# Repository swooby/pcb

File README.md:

# PCBs

NOTE: Unless otherwise specified, **all of these boards are UNTESTED**!

## TODO
* ESP32 with onboard level shifting
* DoubleWing Color Screen with buttons

## Adafruit DoubleWing INA219x4 (quad) Ammeter
Hopefully similar to Adafruit's INA219 FeatherWing (https://www.adafruit.com/product/3650)

## Adafruit FeatherWing INA219x2 (dual) Ammeter
...

## TinyPICO INA219 Ammeter
Hopefully similar to Adafruit's INA219 FeatherWing (https://www.adafruit.com/product/3650)

## TinyPICO 74HCT245 Level Shifter

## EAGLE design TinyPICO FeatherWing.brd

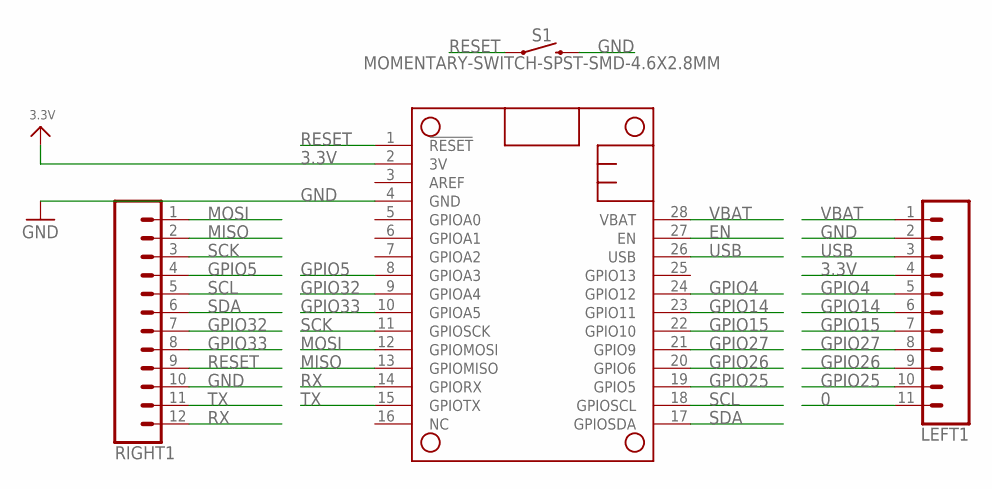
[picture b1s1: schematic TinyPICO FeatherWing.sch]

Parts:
LEFT1: CONN_11; 1X11
MS2: FEATHERWING
RIGHT1: CONN_12; 1X12
S1: MOMENTARY-SWITCH-SPST-SMD-4.6X2.8MM; TACTILE_SWITCH_SMD_4.6X2.8MM

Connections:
0: LEFT1.11
3.3V: LEFT1.4, MS2.2 (3V)
EN: MS2.27 (EN)
GND: LEFT1.2, MS2.4 (GND), RIGHT1.10, S1.3 (2), S1.4 (2)
GPIO4: LEFT1.5, MS2.24 (GPIO12)
GPIO5: MS2.8 (GPIOA3), RIGHT1.4
GPIO14: LEFT1.6, MS2.23 (GPIO11)
GPIO15: LEFT1.7, MS2.22 (GPIO10)
GPIO25: LEFT1.10, MS2.19 (GPIO5)
GPIO26: LEFT1.9, MS2.20 (GPIO6)
GPIO27: LEFT1.8, MS2.21 (GPIO9)
GPIO32: MS2.9 (GPIOA4), RIGHT1.7
GPIO33: MS2.10 (GPIOA5), RIGHT1.8
MISO: MS2.13 (GPIOMISO), RIGHT1.2
MOSI: MS2.12 (GPIOMOSI), RIGHT1.1
RESET: MS2.1 (!RESET), RIGHT1.9, S1.1, S1.2 (1)
RX: MS2.14 (GPIORX), RIGHT1.12
SCK: MS2.11 (GPIOSCK), RIGHT1.3
SCL: MS2.18 (GPIOSCL), RIGHT1.5
SDA: MS2.17 (GPIOSDA), RIGHT1.6
TX: MS2.15 (GPIOTX), RIGHT1.11
USB: LEFT1.3, MS2.26 (USB)
VBAT: LEFT1.1, MS2.28 (VBAT)

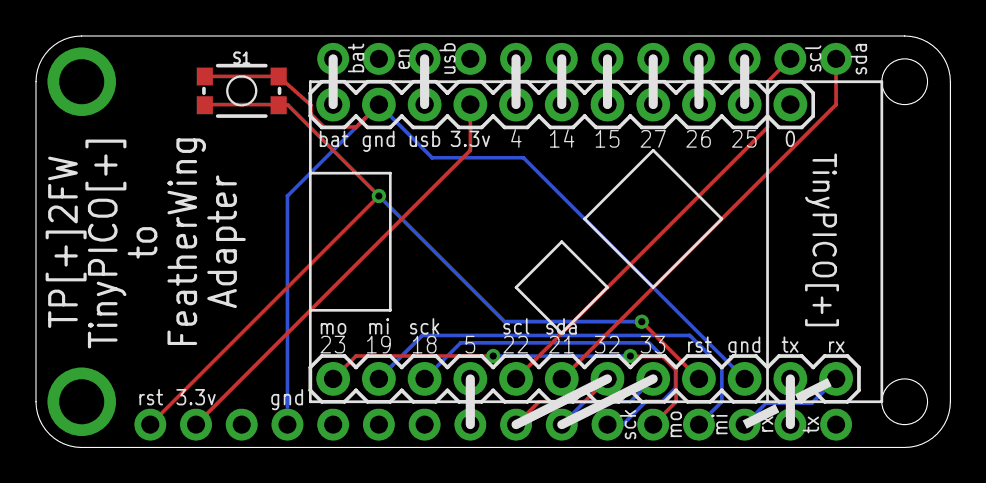
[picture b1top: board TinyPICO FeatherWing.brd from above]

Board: 2 copper layers, 50.8 x 22.9 mm, 4 parts (0 on the bottom side), 21 nets.

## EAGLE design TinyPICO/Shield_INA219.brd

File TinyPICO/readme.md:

* https://github.com/tinypico/tinypico-hardware

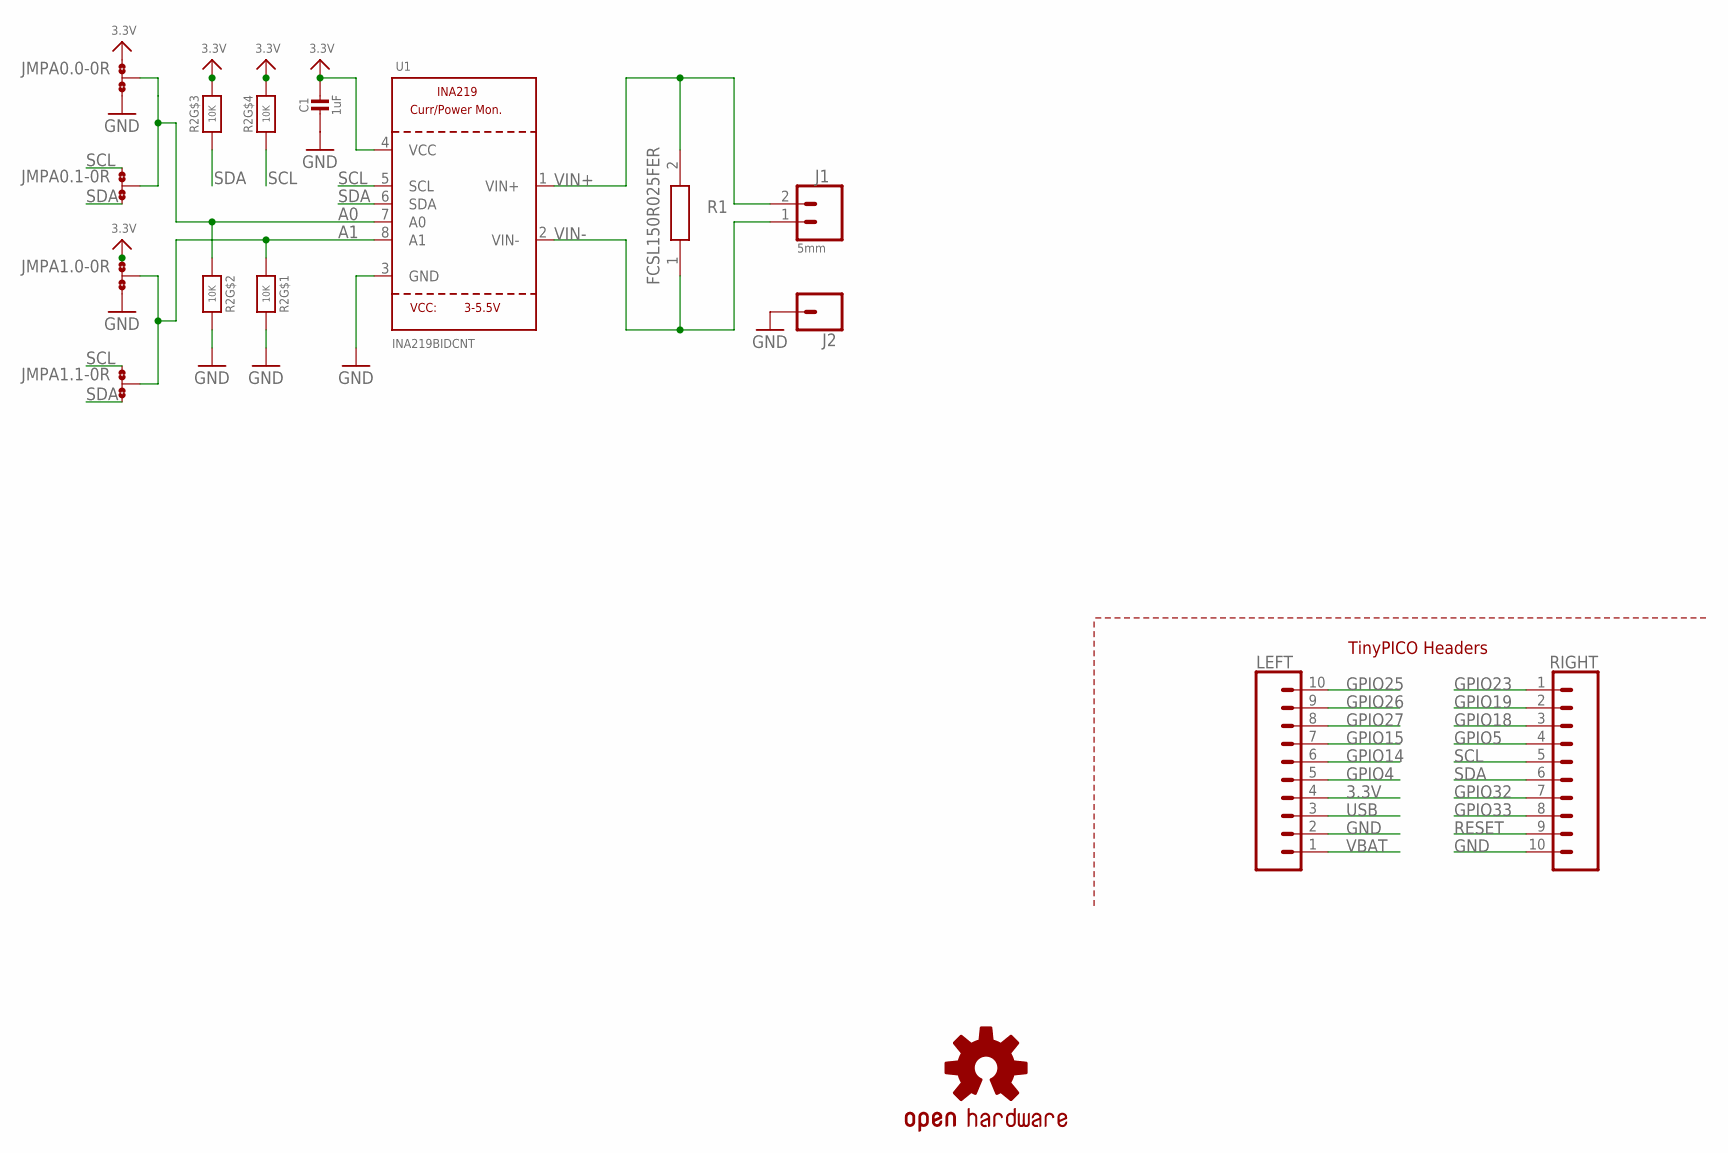
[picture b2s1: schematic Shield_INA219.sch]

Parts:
C1: 1uF; 0805-NO@1
J1: 5mm; SCREWTERMINAL-5MM-2
J2: CONN_01; 1X01
JMPA0.0, JMPA0.1, JMPA1.0, JMPA1.1: 0R-JUMPD; C0R-JMP_NONE
LEFT: TINYPICO_HEADER_10NO_SILK_PTH_FEMALE; 1X10_NO_SILK
LOGO1: OSHW-LOGOS; OSHW-LOGO-S
R1: FCSL150R025FER; RESC90152X87N
R2: 10K; RESPACK_4X0603
RIGHT: TINYPICO_HEADER_10NO_SILK_PTH_FEMALE; 1X10_NO_SILK
U1: INA219BIDCNT; SOT23-8

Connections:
3.3V: C1.1, JMPA0.0.1, JMPA1.0.1, LEFT.4, R2.5 (2), R2.6 (2), U1.4 (VCC)
A0: JMPA0.0.2, JMPA0.1.2, R2.2 (1), U1.7 (A0)
A1: JMPA1.0.2, JMPA1.1.2, R2.1, U1.8 (A1)
GND: C1.2, J2.1, JMPA0.0.3, JMPA1.0.3, LEFT.2, R2.7 (2), R2.8 (2), RIGHT.10, U1.3 (GND)
GPIO4: LEFT.5
GPIO5: RIGHT.4
GPIO14: LEFT.6
GPIO15: LEFT.7
GPIO18: RIGHT.3
GPIO19: RIGHT.2
GPIO23: RIGHT.1
GPIO25: LEFT.10
GPIO26: LEFT.9
GPIO27: LEFT.8
GPIO32: RIGHT.7
GPIO33: RIGHT.8
RESET: RIGHT.9
SCL: JMPA0.1.1, JMPA1.1.1, R2.4 (1), RIGHT.5, U1.5 (SCL)
SDA: JMPA0.1.3, JMPA1.1.3, R2.3 (1), RIGHT.6, U1.6 (SDA)
USB: LEFT.3
VBAT: LEFT.1
VIN+: J1.2, R1.2, U1.1 (VIN+)
VIN-: J1.1, R1.1, U1.2 (VIN-)

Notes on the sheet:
TinyPICO Headers

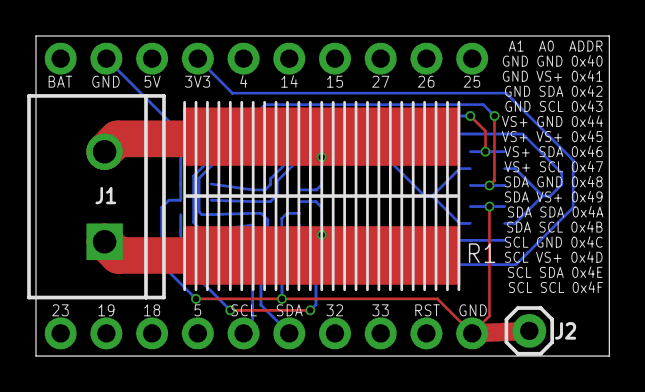
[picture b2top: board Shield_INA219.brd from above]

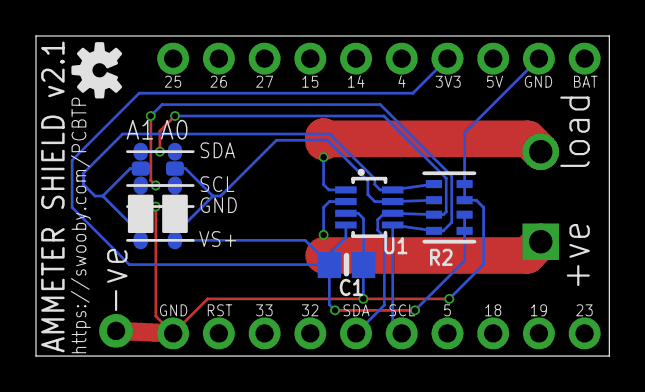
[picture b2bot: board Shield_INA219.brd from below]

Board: 2 copper layers, 31.9 x 17.8 mm, 13 parts (8 on the bottom side), 8 nets.

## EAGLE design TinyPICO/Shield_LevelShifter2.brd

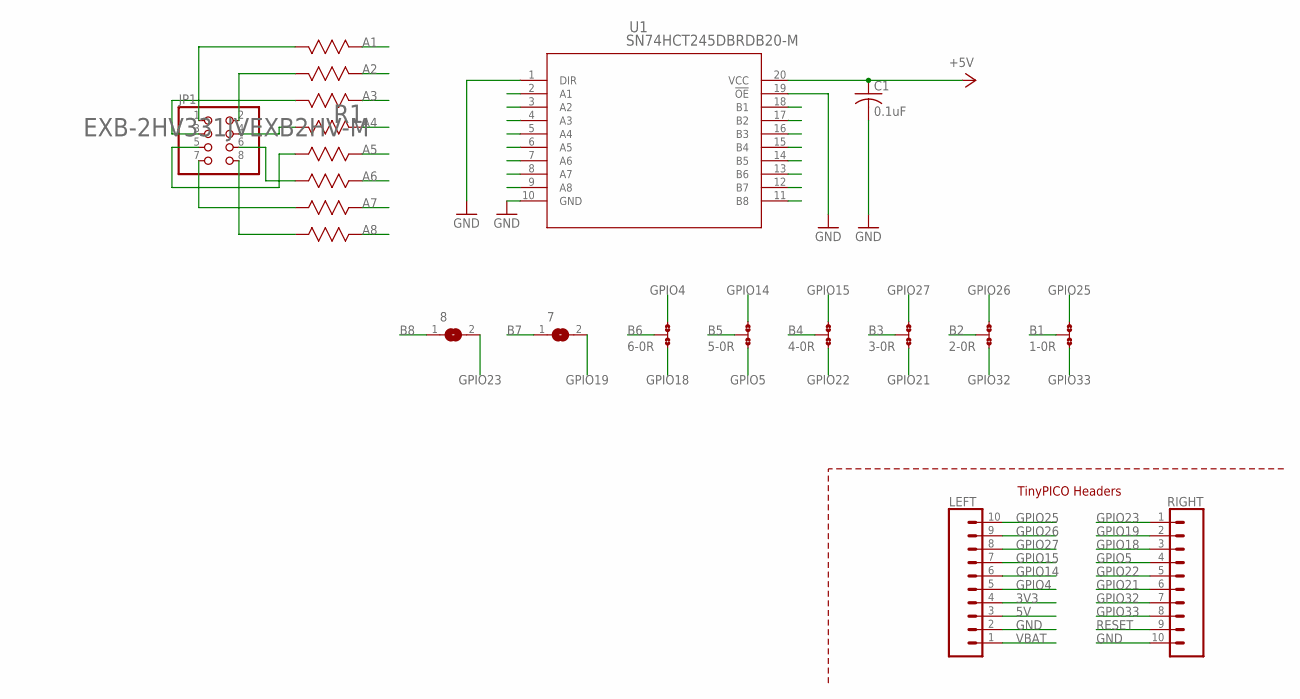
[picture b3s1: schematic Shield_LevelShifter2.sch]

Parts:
1, 2, 3, 4, 5, 6: 0R-JUMPD; C0R-JMP_NONE
7, 8: SJ
C1: 0.1uF; C0603
JP1: PINHD-2X4/90; 2X04/90
LEFT: TINYPICO_HEADER_10NO_SILK_PTH_FEMALE; 1X10_NO_SILK
R1: EXB-2HV331JVEXB2HV-M; EXB2HV-M
RIGHT: TINYPICO_HEADER_10NO_SILK_PTH_FEMALE; 1X10_NO_SILK
U1: SN74HCT245DBRDB20-M; DB20-M

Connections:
3V3: LEFT.4
5V: C1.1, LEFT.3, U1.20 (VCC)
A1: R1.1, U1.2 (A1)
A2: R1.2, U1.3 (A2)
A3: R1.3, U1.4 (A3)
A4: R1.4, U1.5 (A4)
A5: R1.5, U1.6 (A5)
A6: R1.6, U1.7 (A6)
A7: R1.7, U1.8 (A7)
A8: R1.8, U1.9 (A8)
B1: 1.2, U1.18 (B1)
B2: 2.2, U1.17 (B2)
B3: 3.2, U1.16 (B3)
B4: 4.2, U1.15 (B4)
B5: 5.2, U1.14 (B5)
B6: 6.2, U1.13 (B6)
B7: 7.1, U1.12 (B7)
B8: 8.1, U1.11 (B8)
GND: C1.2, LEFT.2, RIGHT.10, U1.1 (DIR), U1.10 (GND), U1.19 (!OE)
GPIO4: 6.3, LEFT.5
GPIO5: 5.1, RIGHT.4
GPIO14: 5.3, LEFT.6
GPIO15: 4.3, LEFT.7
GPIO18: 6.1, RIGHT.3
GPIO19: 7.2, RIGHT.2
GPIO21: 3.1, RIGHT.6
GPIO22: 4.1, RIGHT.5
GPIO23: 8.2, RIGHT.1
GPIO25: 1.3, LEFT.10
GPIO26: 2.3, LEFT.9
GPIO27: 3.3, LEFT.8
GPIO32: 2.1, RIGHT.7
GPIO33: 1.1, RIGHT.8
unnamed: JP1.1, R1.16
unnamed: JP1.4, R1.13
unnamed: JP1.2, R1.15
unnamed: JP1.3, R1.14
unnamed: JP1.5, R1.12
unnamed: JP1.6, R1.11
unnamed: JP1.7, R1.10
unnamed: JP1.8, R1.9
RESET: RIGHT.9
VBAT: LEFT.1

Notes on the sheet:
TinyPICO Headers

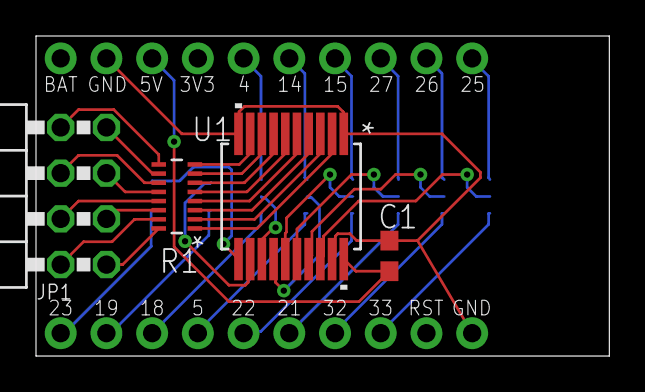
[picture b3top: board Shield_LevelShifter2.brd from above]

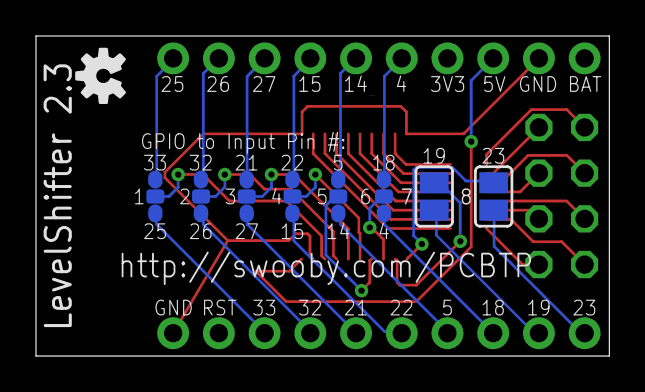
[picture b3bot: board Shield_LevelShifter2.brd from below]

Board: 2 copper layers, 31.9 x 17.8 mm, 15 parts (9 on the bottom side), 40 nets.

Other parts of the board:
LOGO: OSHW-LOGOS; OSHW-LOGO-S

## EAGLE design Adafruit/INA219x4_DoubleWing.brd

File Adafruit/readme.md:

* https://github.com/adafruit/Adafruit-INA219-Current-Sensor-PCB
* https://github.com/adafruit/Adafruit-FeatherWing-Proto-Doubler-and-Tripler

* https://github.com/adafruit/Adafruit-HUZZAH32-ESP32-Feather-PCB
* https://github.com/adafruit/Adafruit-Terminal-Block-FeatherWing-PCB
* https://github.com/adafruit/Adafruit-OLED-FeatherWing-PCB
* https://github.com/adafruit/Adafruit_FeatherOLED
* https://github.com/adafruit/Adafruit-NeoPixel-FeatherWing-PCB
* https://github.com/adafruit/Adafruit-Ethernet-FeatherWing-PCB
* https://github.com/adafruit/Adafruit-RGB-Matrix-FeatherWing-PCB
* https://github.com/adafruit/Adafruit-3.5in-TFT-Featherwing-PCB
* https://github.com/adafruit/Adafruit-2.4-TFT-FeatherWing-PCB
* https://github.com/adafruit/Adafruit-Mini-TFT-with-Joystick-Featherwing-PCB
* https://github.com/adafruit/Adafruit-Joy-Featherwing-PCB

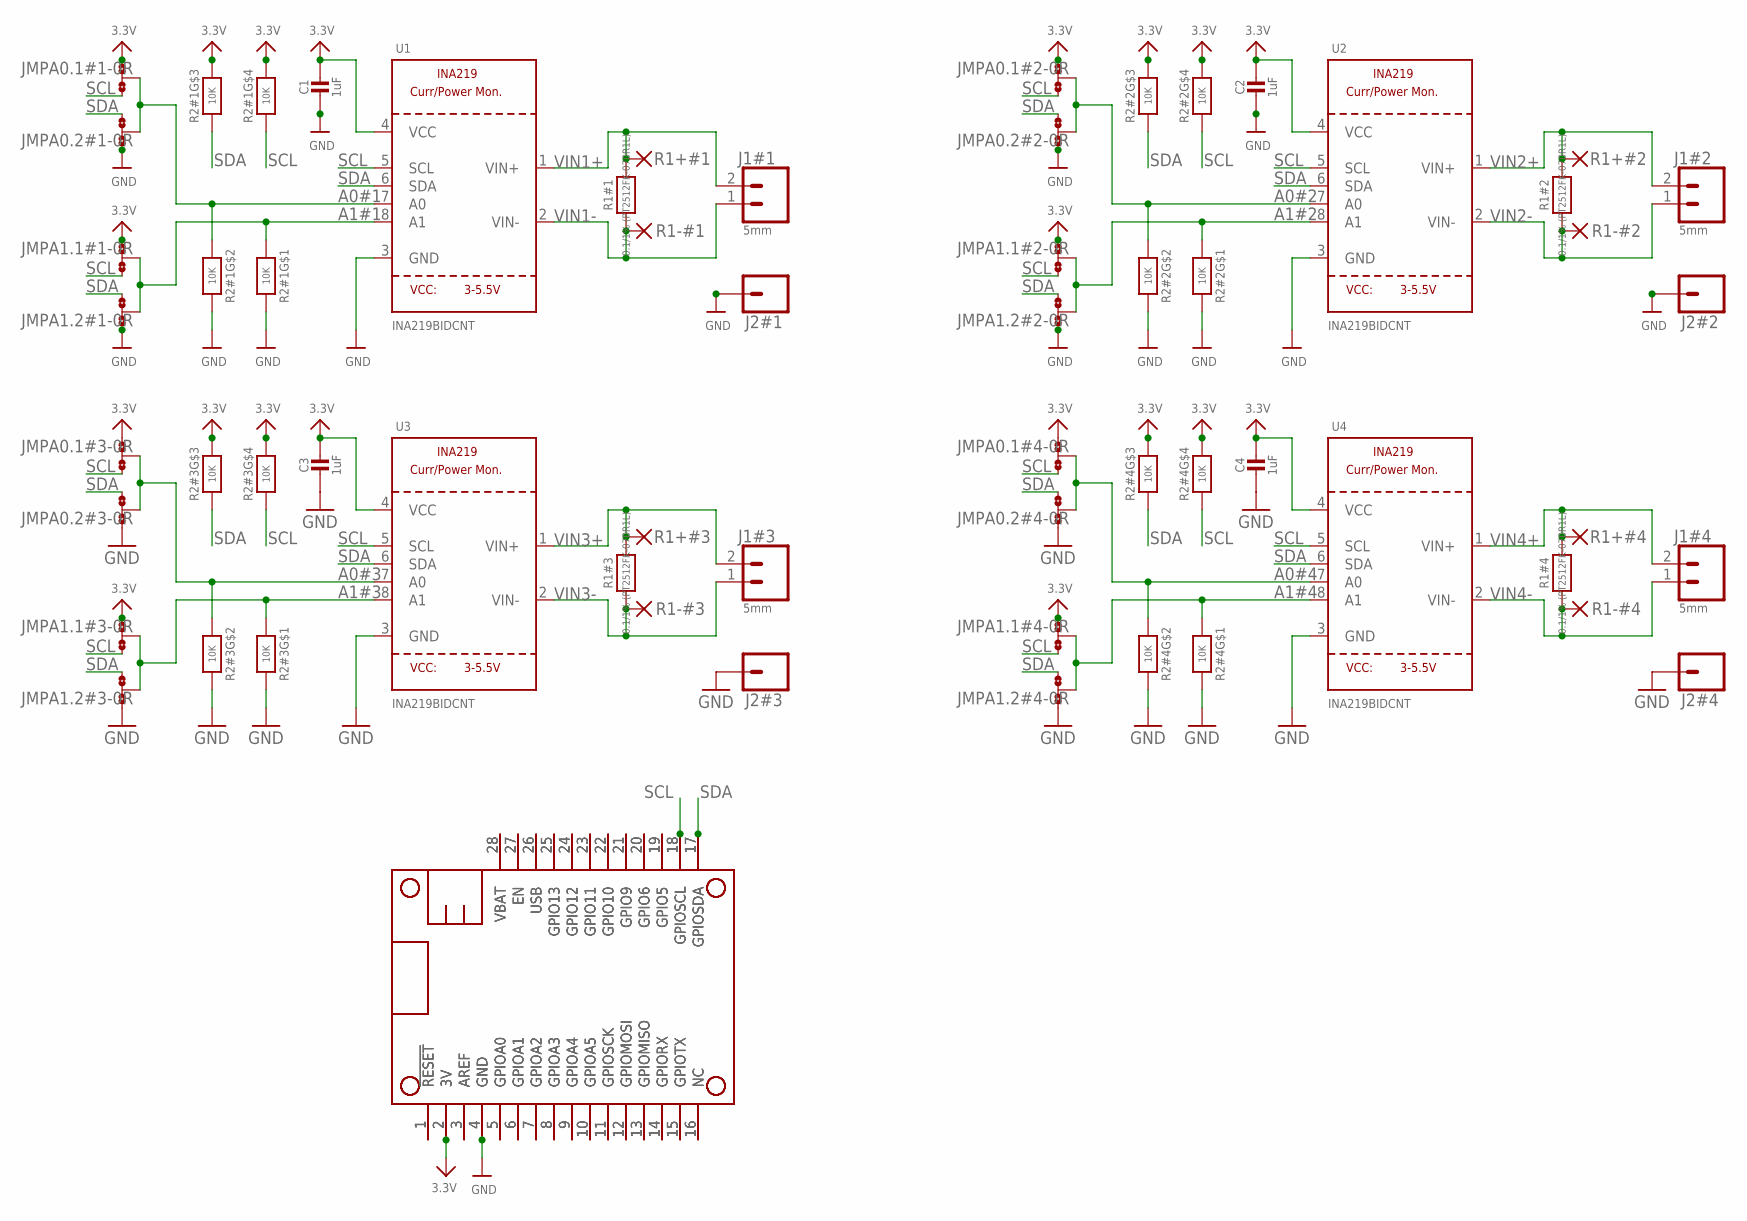
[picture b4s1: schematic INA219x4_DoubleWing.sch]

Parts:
C1, C2, C3, C4: 1uF; 0805-NO@1
J1#1, J1#2, J1#3, J1#4: 5mm; SCREWTERMINAL-5MM-2
J2#1, J2#2, J2#3, J2#4: CONN_01; 1X01
JMPA0.1#1, JMPA0.1#2, JMPA0.1#3, JMPA0.1#4, JMPA0.2#1, JMPA0.2#2, JMPA0.2#3, JMPA0.2#4, JMPA1.1#1, JMPA1.1#2, JMPA1.1#3, JMPA1.1#4, JMPA1.2#1, JMPA1.2#2, JMPA1.2#3, JMPA1.2#4: 0R-JUMPD; C0R-JMP_NONE
MS1, MS2: FEATHERWING_NODIM; FEATHERWING_DIM
R1#1, R1#2, R1#3, R1#4: 0.1/1% (PT2512FK-070R1L); 2512
R1+#1, R1+#2, R1+#3, R1+#4, R1-#1, R1-#2, R1-#3, R1-#4: 1,6/0,9
R2#1, R2#2, R2#3, R2#4: 10K; RESPACK_4X0603
U1, U2, U3, U4: INA219BIDCNT; SOT23-8

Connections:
3.3V: C1.1, C2.1, C3.1, C4.1, JMPA0.1#1.1, JMPA0.1#2.1, JMPA0.1#3.1, JMPA0.1#4.1, JMPA1.1#1.1, JMPA1.1#2.1, JMPA1.1#3.1, JMPA1.1#4.1, MS1.2 (3V), MS2.2 (3V), R2#1.5 (2), R2#1.6 (2), R2#2.5 (2), R2#2.6 (2), R2#3.5 (2), R2#3.6 (2), R2#4.5 (2), R2#4.6 (2), U1.4 (VCC), U2.4 (VCC), U3.4 (VCC), U4.4 (VCC)
A0#1: JMPA0.1#1.2, JMPA0.2#1.2, R2#1.2 (1), U1.7 (A0)
A0#2: JMPA0.1#2.2, JMPA0.2#2.2, R2#2.2 (1), U2.7 (A0)
A0#3: JMPA0.1#3.2, JMPA0.2#3.2, R2#3.2 (1), U3.7 (A0)
A0#4: JMPA0.1#4.2, JMPA0.2#4.2, R2#4.2 (1), U4.7 (A0)
A1#1: JMPA1.1#1.2, JMPA1.2#1.2, R2#1.1, U1.8 (A1)
A1#2: JMPA1.1#2.2, JMPA1.2#2.2, R2#2.1, U2.8 (A1)
A1#3: JMPA1.1#3.2, JMPA1.2#3.2, R2#3.1, U3.8 (A1)
A1#4: JMPA1.1#4.2, JMPA1.2#4.2, R2#4.1, U4.8 (A1)
GND: C1.2, C2.2, C3.2, C4.2, J2#1.1, J2#2.1, J2#3.1, J2#4.1, JMPA0.2#1.3, JMPA0.2#2.3, JMPA0.2#3.3, JMPA0.2#4.3, JMPA1.2#1.3, JMPA1.2#2.3, JMPA1.2#3.3, JMPA1.2#4.3, MS1.4 (GND), MS2.4 (GND), R2#1.7 (2), R2#1.8 (2), R2#2.7 (2), R2#2.8 (2), R2#3.7 (2), R2#3.8 (2), R2#4.7 (2), R2#4.8 (2), U1.3 (GND), U2.3 (GND), U3.3 (GND), U4.3 (GND)
unnamed: MS1.27 (EN), MS2.27 (EN)
unnamed: MS1.16 (NC), MS2.16 (NC)
unnamed: MS1.25 (GPIO13), MS2.25 (GPIO13)
unnamed: MS1.15 (GPIOTX), MS2.15 (GPIOTX)
unnamed: MS1.24 (GPIO12), MS2.24 (GPIO12)
unnamed: MS1.14 (GPIORX), MS2.14 (GPIORX)
unnamed: MS1.13 (GPIOMISO), MS2.13 (GPIOMISO)
unnamed: MS1.12 (GPIOMOSI), MS2.12 (GPIOMOSI)
unnamed: MS1.11 (GPIOSCK), MS2.11 (GPIOSCK)
unnamed: MS1.10 (GPIOA5), MS2.10 (GPIOA5)
unnamed: MS1.9 (GPIOA4), MS2.9 (GPIOA4)
unnamed: MS1.8 (GPIOA3), MS2.8 (GPIOA3)
unnamed: MS1.7 (GPIOA2), MS2.7 (GPIOA2)
unnamed: MS1.6 (GPIOA1), MS2.6 (GPIOA1)
unnamed: MS1.5 (GPIOA0), MS2.5 (GPIOA0)
unnamed: MS1.3 (AREF), MS2.3 (AREF)
unnamed: MS1.1 (!RESET), MS2.1 (!RESET)
unnamed: MS1.23 (GPIO11), MS2.23 (GPIO11)
unnamed: MS1.22 (GPIO10), MS2.22 (GPIO10)
unnamed: MS1.21 (GPIO9), MS2.21 (GPIO9)
unnamed: MS1.20 (GPIO6), MS2.20 (GPIO6)
unnamed: MS1.19 (GPIO5), MS2.19 (GPIO5)
SCL: JMPA0.1#1.3, JMPA0.1#2.3, JMPA0.1#3.3, JMPA0.1#4.3, JMPA1.1#1.3, JMPA1.1#2.3, JMPA1.1#3.3, JMPA1.1#4.3, MS1.18 (GPIOSCL), MS2.18 (GPIOSCL), R2#1.4 (1), R2#2.4 (1), R2#3.4 (1), R2#4.4 (1), U1.5 (SCL), U2.5 (SCL), U3.5 (SCL), U4.5 (SCL)
SDA: JMPA0.2#1.1, JMPA0.2#2.1, JMPA0.2#3.1, JMPA0.2#4.1, JMPA1.2#1.1, JMPA1.2#2.1, JMPA1.2#3.1, JMPA1.2#4.1, MS1.17 (GPIOSDA), MS2.17 (GPIOSDA), R2#1.3 (1), R2#2.3 (1), R2#3.3 (1), R2#4.3 (1), U1.6 (SDA), U2.6 (SDA), U3.6 (SDA), U4.6 (SDA)
USB: MS1.26 (USB), MS2.26 (USB)
VBAT: MS1.28 (VBAT), MS2.28 (VBAT)
VIN1+: J1#1.2, R1#1.2, R1+#1.1, U1.1 (VIN+)
VIN1-: J1#1.1, R1#1.1, R1-#1.1, U1.2 (VIN-)
VIN2+: J1#2.2, R1#2.2, R1+#2.1, U2.1 (VIN+)
VIN2-: J1#2.1, R1#2.1, R1-#2.1, U2.2 (VIN-)
VIN3+: J1#3.2, R1#3.2, R1+#3.1, U3.1 (VIN+)
VIN3-: J1#3.1, R1#3.1, R1-#3.1, U3.2 (VIN-)
VIN4+: J1#4.2, R1#4.2, R1+#4.1, U4.1 (VIN+)
VIN4-: J1#4.1, R1#4.1, R1-#4.1, U4.2 (VIN-)

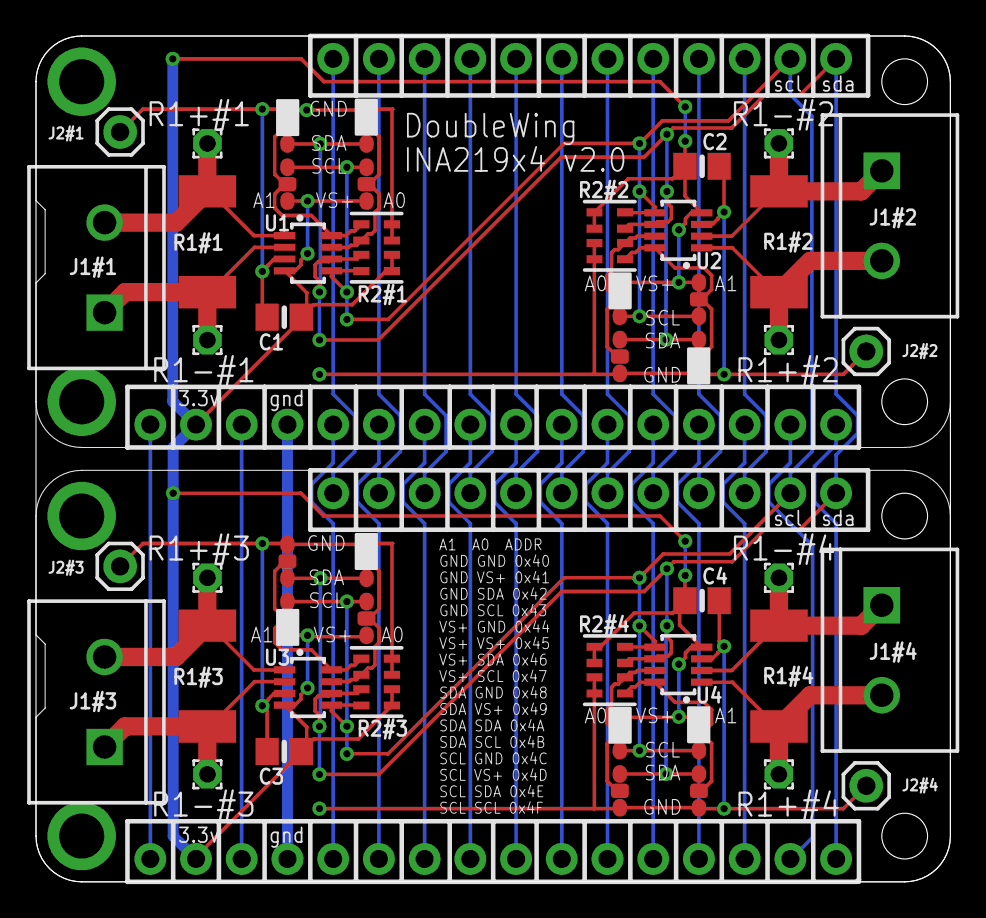
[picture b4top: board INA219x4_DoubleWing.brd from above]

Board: 2 copper layers, 50.8 x 47.0 mm, 50 parts (0 on the bottom side), 44 nets.

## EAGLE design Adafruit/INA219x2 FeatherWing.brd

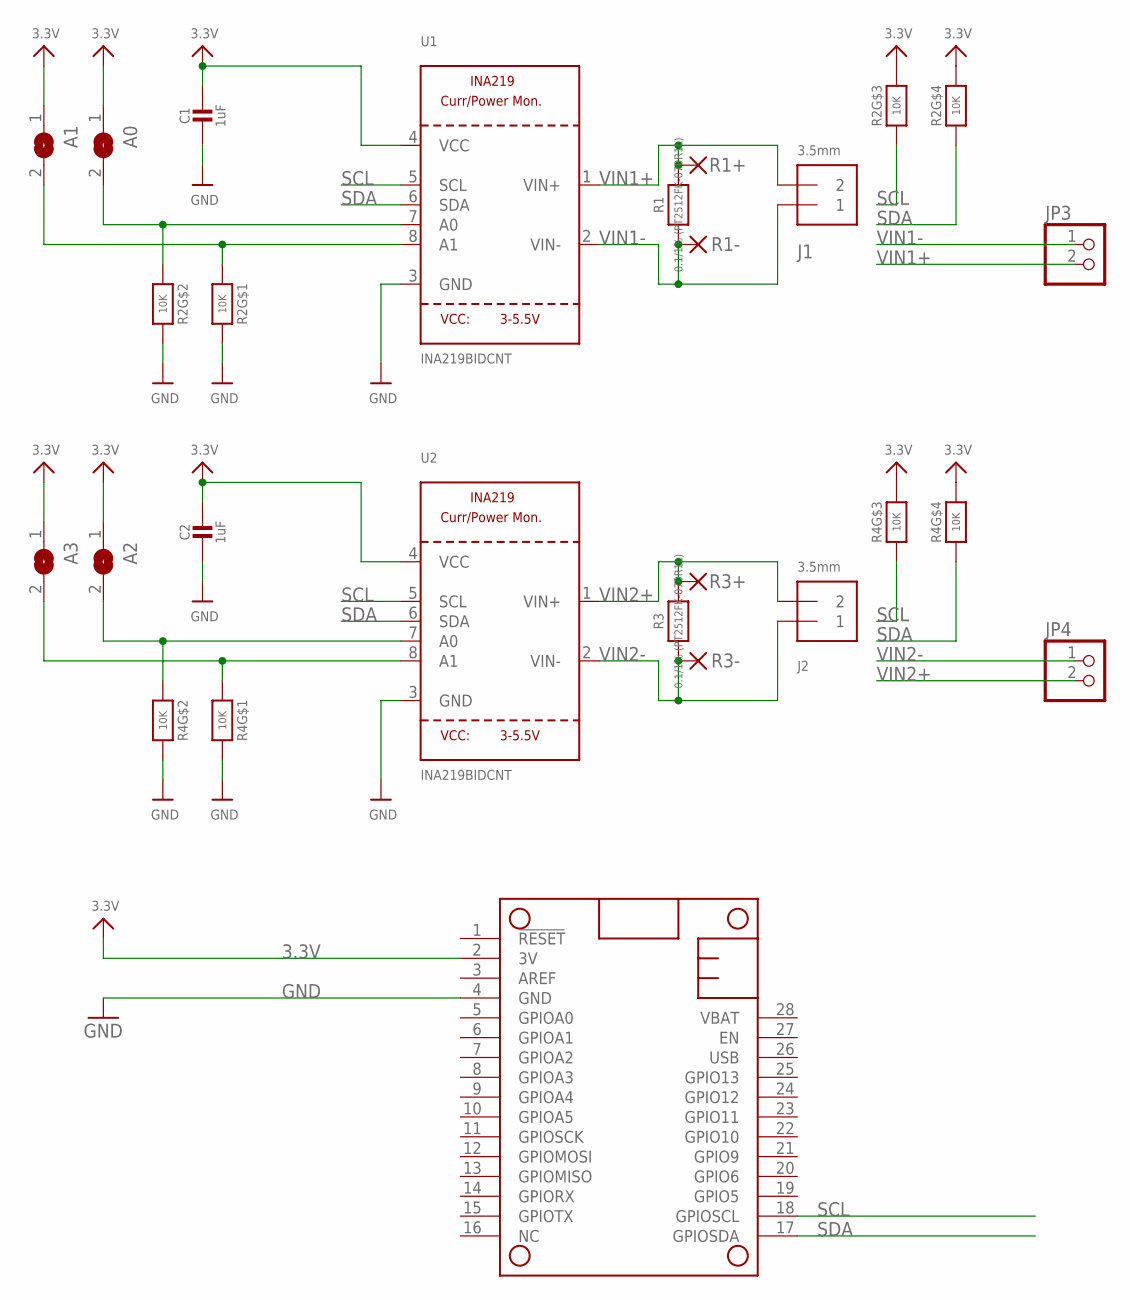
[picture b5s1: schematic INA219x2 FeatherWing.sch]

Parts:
A0, A1, A2, A3: SOLDERJUMPERREFLOW_NOPASTE; SOLDERJUMPER_REFLOW_NOPASTE
C1, C2: 1uF; 0805-NO@1
J1, J2: 3.5mm; TERMBLOCK_1X2-3.5MM
JP3, JP4: HEADER-1X2ROUND; 1X02_ROUND
MS1: FEATHERWING
R1, R3: 0.1/1% (PT2512FK-070R1L); 2512
R1+, R1-, R3+, R3-: 1,6/0,9
R2, R4: 10K; RESPACK_4X0603
U1, U2: INA219BIDCNT; SOT23-8

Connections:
3.3V: A0.1, A1.1, A2.1, A3.1, C1.1, C2.1, MS1.2 (3V), R2.5 (2), R2.6 (2), R4.5 (2), R4.6 (2), U1.4 (VCC), U2.4 (VCC)
GND: C1.2, C2.2, MS1.4 (GND), R2.7 (2), R2.8 (2), R4.7 (2), R4.8 (2), U1.3 (GND), U2.3 (GND)
unnamed: A1.2, R2.1, U1.8 (A1)
unnamed: A0.2, R2.2 (1), U1.7 (A0)
unnamed: A3.2, R4.1, U2.8 (A1)
unnamed: A2.2, R4.2 (1), U2.7 (A0)
SCL: MS1.18 (GPIOSCL), R2.3 (1), R4.3 (1), U1.5 (SCL), U2.5 (SCL)
SDA: MS1.17 (GPIOSDA), R2.4 (1), R4.4 (1), U1.6 (SDA), U2.6 (SDA)
VIN1+: J1.2, JP3.2, R1.2, R1+.1, U1.1 (VIN+)
VIN1-: J1.1, JP3.1, R1.1, R1-.1, U1.2 (VIN-)
VIN2+: J2.2, JP4.2, R3.2, R3+.1, U2.1 (VIN+)
VIN2-: J2.1, JP4.1, R3.1, R3-.1, U2.2 (VIN-)

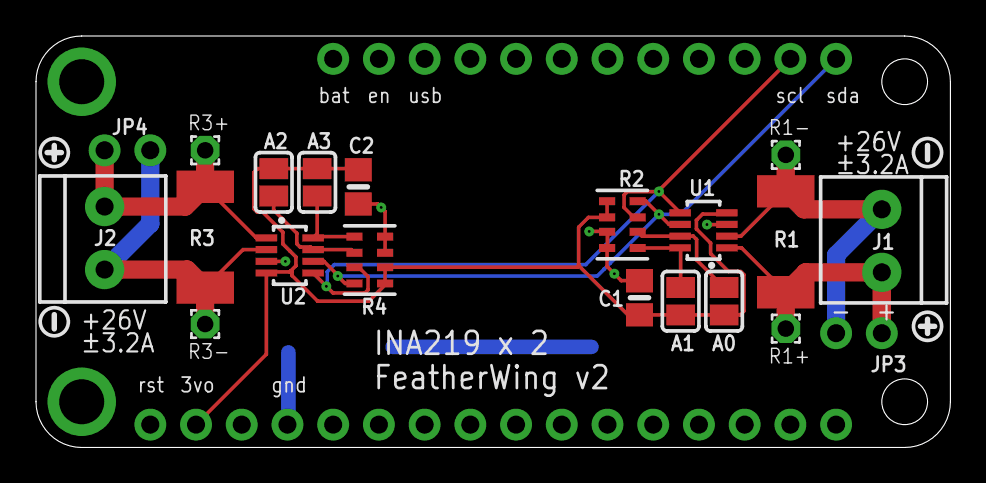
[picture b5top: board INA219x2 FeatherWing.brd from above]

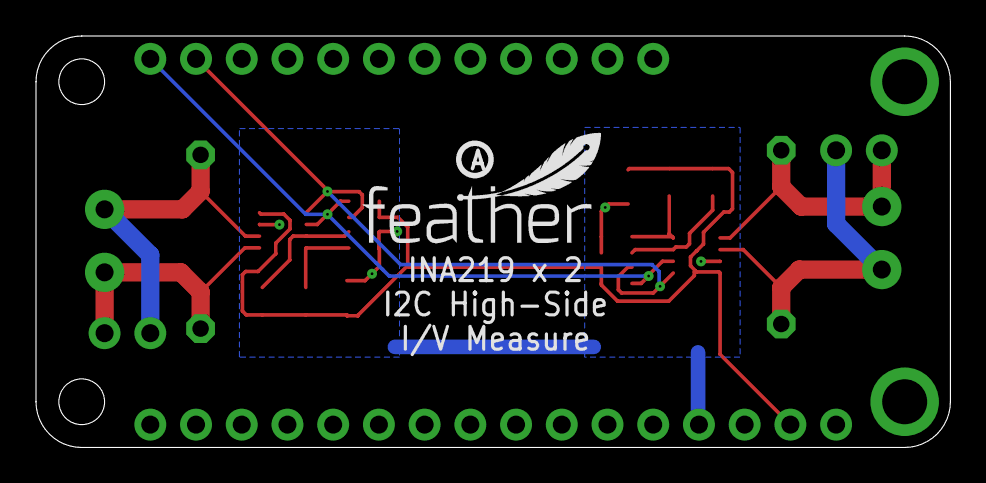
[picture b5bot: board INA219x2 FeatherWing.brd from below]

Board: 2 copper layers, 50.8 x 22.9 mm, 27 parts (2 on the bottom side), 12 nets.

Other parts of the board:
U$12, U$14: SYMBOL_PLUS
U$13, U$16: SYMBOL_MINUS
U$15: FEATHERLOGO_SMALL
U$17: PCBFEAT-REV-040

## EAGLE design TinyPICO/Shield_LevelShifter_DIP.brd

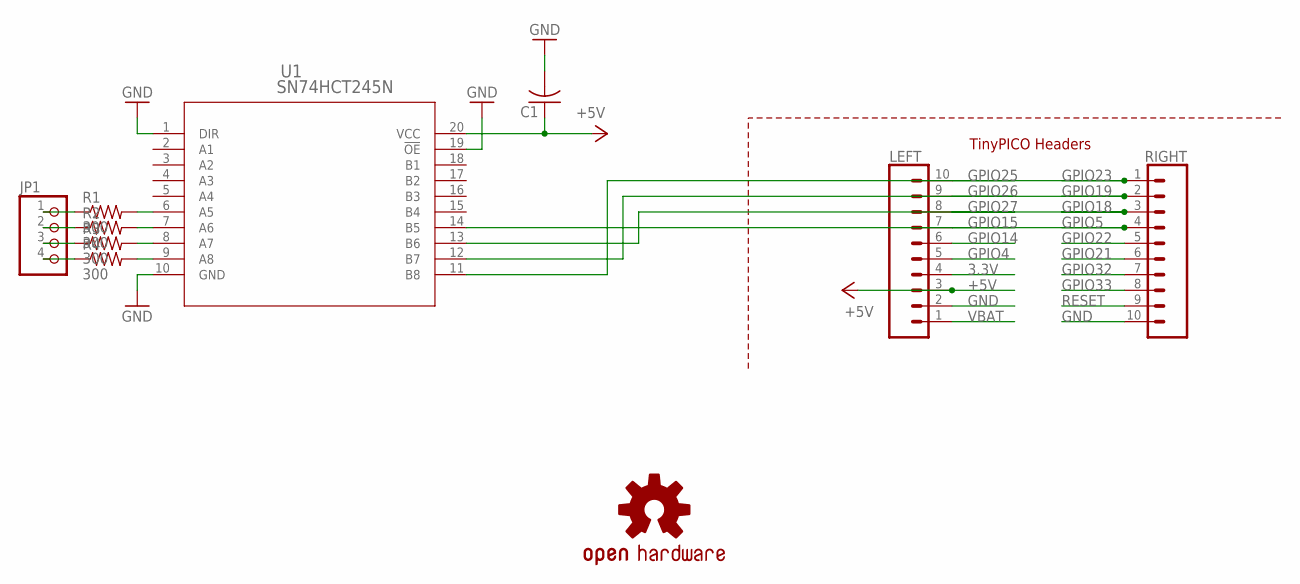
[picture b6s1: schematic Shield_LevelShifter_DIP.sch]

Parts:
C1: C-US025-025X050; C025-025X050
JP1: PINHD-1X4; 1X04
LEFT: TINYPICO_HEADER_10NO_SILK_PTH_FEMALE; 1X10_NO_SILK
LOGO1: OSHW-LOGOS; OSHW-LOGO-S
R1, R2, R3, R4: 300; 0204V
RIGHT: TINYPICO_HEADER_10NO_SILK_PTH_FEMALE; 1X10_NO_SILK
U1: SN74HCT245N; N20

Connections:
3.3V: LEFT.4
+5V: C1.1, LEFT.3, U1.20 (VCC)
GND: C1.2, LEFT.2, RIGHT.10, U1.1 (DIR), U1.10 (GND), U1.19 (!OE)
GPIO4: LEFT.5
GPIO5: RIGHT.4, U1.14 (B5)
GPIO14: LEFT.6
GPIO15: LEFT.7
GPIO18: RIGHT.3, U1.13 (B6)
GPIO19: RIGHT.2, U1.12 (B7)
GPIO21: RIGHT.6
GPIO22: RIGHT.5
GPIO23: RIGHT.1, U1.11 (B8)
GPIO25: LEFT.10
GPIO26: LEFT.9
GPIO27: LEFT.8
GPIO32: RIGHT.7
GPIO33: RIGHT.8
unnamed: R1.2, U1.6 (A5)
unnamed: R2.2, U1.7 (A6)
unnamed: R3.2, U1.8 (A7)
unnamed: R4.2, U1.9 (A8)
unnamed: JP1.1, R1.1
unnamed: JP1.2, R2.1
unnamed: JP1.3, R3.1
unnamed: JP1.4, R4.1
RESET: RIGHT.9
VBAT: LEFT.1

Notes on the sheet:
TinyPICO Headers

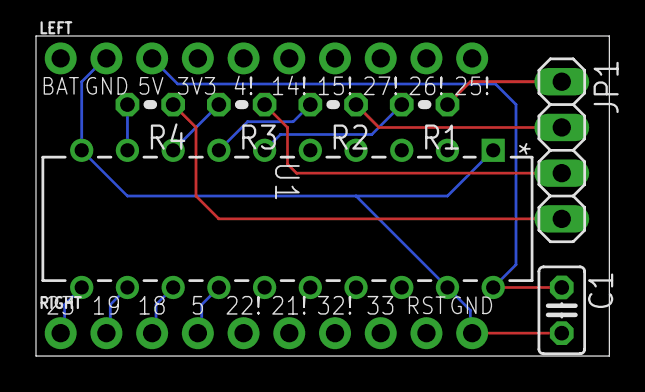
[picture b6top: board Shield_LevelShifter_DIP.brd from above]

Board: 2 copper layers, 31.9 x 17.8 mm, 10 parts (1 on the bottom side), 14 nets.

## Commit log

2019-07-19 Initial TinyPICO LevelShifter (DIP version)
2019-07-19 Tiny output signal tweak
2019-07-23 Current progress checkpoint
2019-07-23 Prettied up the boards a little
2019-07-23 Adding some screenshots for the WIP levelshifter
2019-07-23 Renaming files
2019-07-23 Missed some renames
2019-07-23 Adding schematic backup to .gitignore
2019-07-23 Prettier
2019-07-24 INA219 FeatherWing v2
2019-07-25 Adding DoubleWing based INA219x4 (quad)
2019-07-25 Adding images of INA219x4
2019-07-25 Renaming "INA219x4 FeatherWing" to "INA219x4 DoubleWing"
2019-07-25 Moving subfolder readme.md to root
2019-07-25 Fix formatting
2019-07-25 Fixing readme markup
2019-07-26 Updated to version that was sent to oshpark for fabrication
2019-07-26 Lower res
2019-07-26 Renaming to remove white space
2019-07-27 DoubleWing INA219x4 v1.1: Better labels!
2019-07-31 INA219x4 DoubleWing v2.0
2019-07-31 Forgot to cleaned ratnest to get groundplane
2019-07-31 Adding DoubleWing Blank
2019-08-01 Adding TinyPICO LevelShifter (SMT)
2019-08-01 Uploading images
2019-08-01 Fixing some ERC/DRC errors
2019-08-02 Rotated the board per Seon's suggestion
2019-08-02 Renaming LevelShifter1 and LevelShifter2
2019-08-03 Adding FeatherWing_Blank
2019-08-04 Checkpoint
2019-08-08 Adding TinyPICO and 3up shield
2019-08-09 Removed TinyPICO logos (per license & request of Seon)
2019-08-16 TinyPICO Shield Ammeter INA219 v2.1
2019-09-15 TinyPICO FeatherWing
2019-09-16 Tiny tweak to Reset trace
2019-09-20 Adding Adafruit 2.8 inch TFT w Capacitive Touch

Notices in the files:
parts and their libraries:
SparkFun-Connectors: Licensing: Creative Commons ShareAlike 4.0 International - https://creativecommons.org/licenses/by-sa/4.0
